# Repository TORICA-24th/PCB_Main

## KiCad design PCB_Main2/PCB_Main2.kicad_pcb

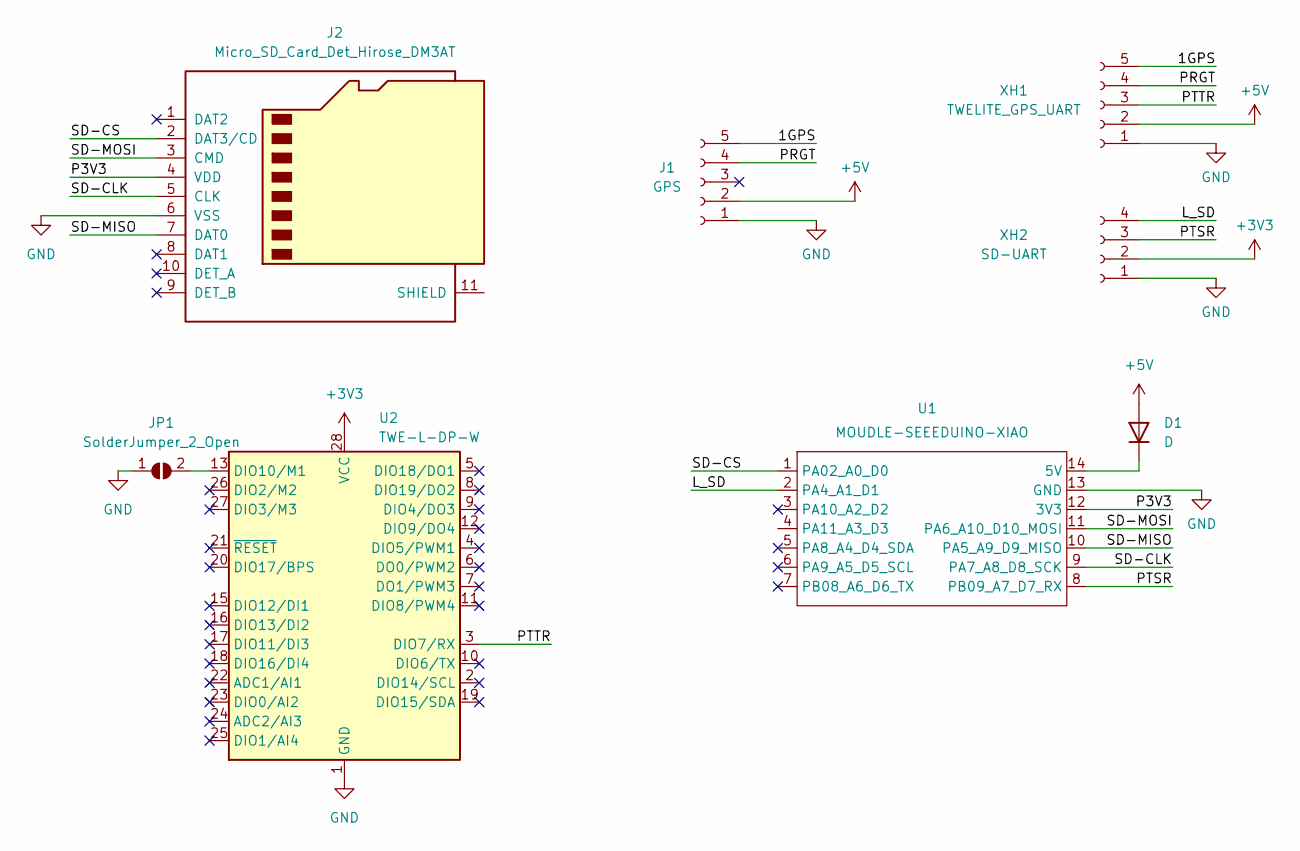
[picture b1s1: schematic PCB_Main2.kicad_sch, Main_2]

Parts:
D1: D; D_A-405_P10.16mm_Horizontal
J1: GPS; JST_XH_S5B-XH-A_1x05_P2.50mm_Horizontal
J2: Micro_SD_Card_Det_Hirose_DM3AT; microSD_AE-MICRO-SD-DIP
JP1: SolderJumper_2_Open; SolderJumper-2_P1.3mm_Open_RoundedPad1.0x1.5mm
U1: MOUDLE-SEEEDUINO-XIAO; MOUDLE14P-2.54-21X17.8MM
U2: TWE-L-DP-W; DIP-28_W15.24mm
XH1: TWELITE_GPS_UART; JST_XH_S5B-XH-A_1x05_P2.50mm_Horizontal
XH2: SD-UART; JST_XH_S4B-XH-A_1x04_P2.50mm_Horizontal

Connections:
+3V3: U2.28 (VCC), XH2.2
+5V: D1.2 (A), J1.2, XH1.2
/1GPS: J1.5, XH1.5
/L_SD: U1.2 (PA4_A1_D1), XH2.4
/P3V3: J2.4 (VDD), U1.12 (3V3)
/PRGT: J1.4, XH1.4
/PTSR: U1.8 (PB09_A7_D7_RX), XH2.3
/PTTR: U2.3 (DIO7/RX), XH1.3
/SD-CLK: J2.5 (CLK), U1.9 (PA7_A8_D8_SCK)
/SD-CS: J2.2 (DAT3/CD), U1.1 (PA02_A0_D0)
/SD-MISO: J2.7 (DAT0), U1.10 (PA5_A9_D9_MISO)
/SD-MOSI: J2.3 (CMD), U1.11 (PA6_A10_D10_MOSI)
GND: J1.1, J2.6 (VSS), JP1.1 (A), U1.13 (GND), U2.1 (GND), U2.14 (GND), XH1.1, XH2.1
unnamed: D1.1 (K), U1.14 (5V)
unnamed: JP1.2 (B), U2.13 (DIO10/M1)

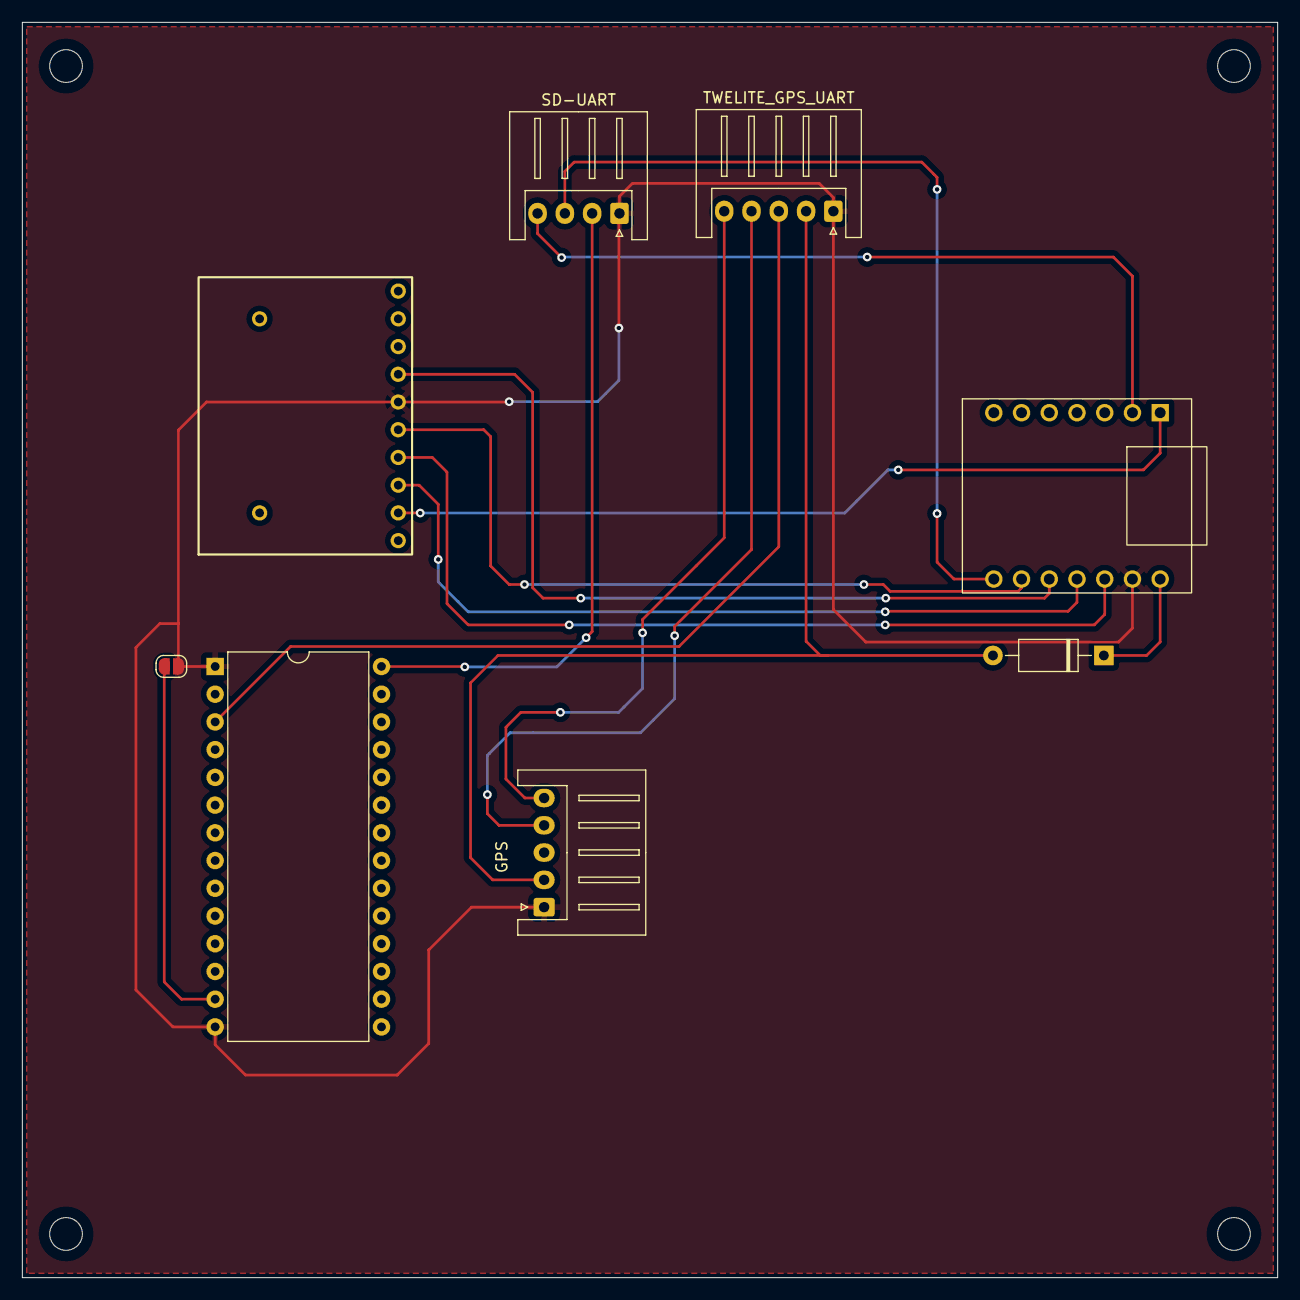
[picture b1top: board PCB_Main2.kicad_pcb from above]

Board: 2 copper layers, 115.0 x 115.0 mm, 8 parts (0 on the bottom side), 15 nets.

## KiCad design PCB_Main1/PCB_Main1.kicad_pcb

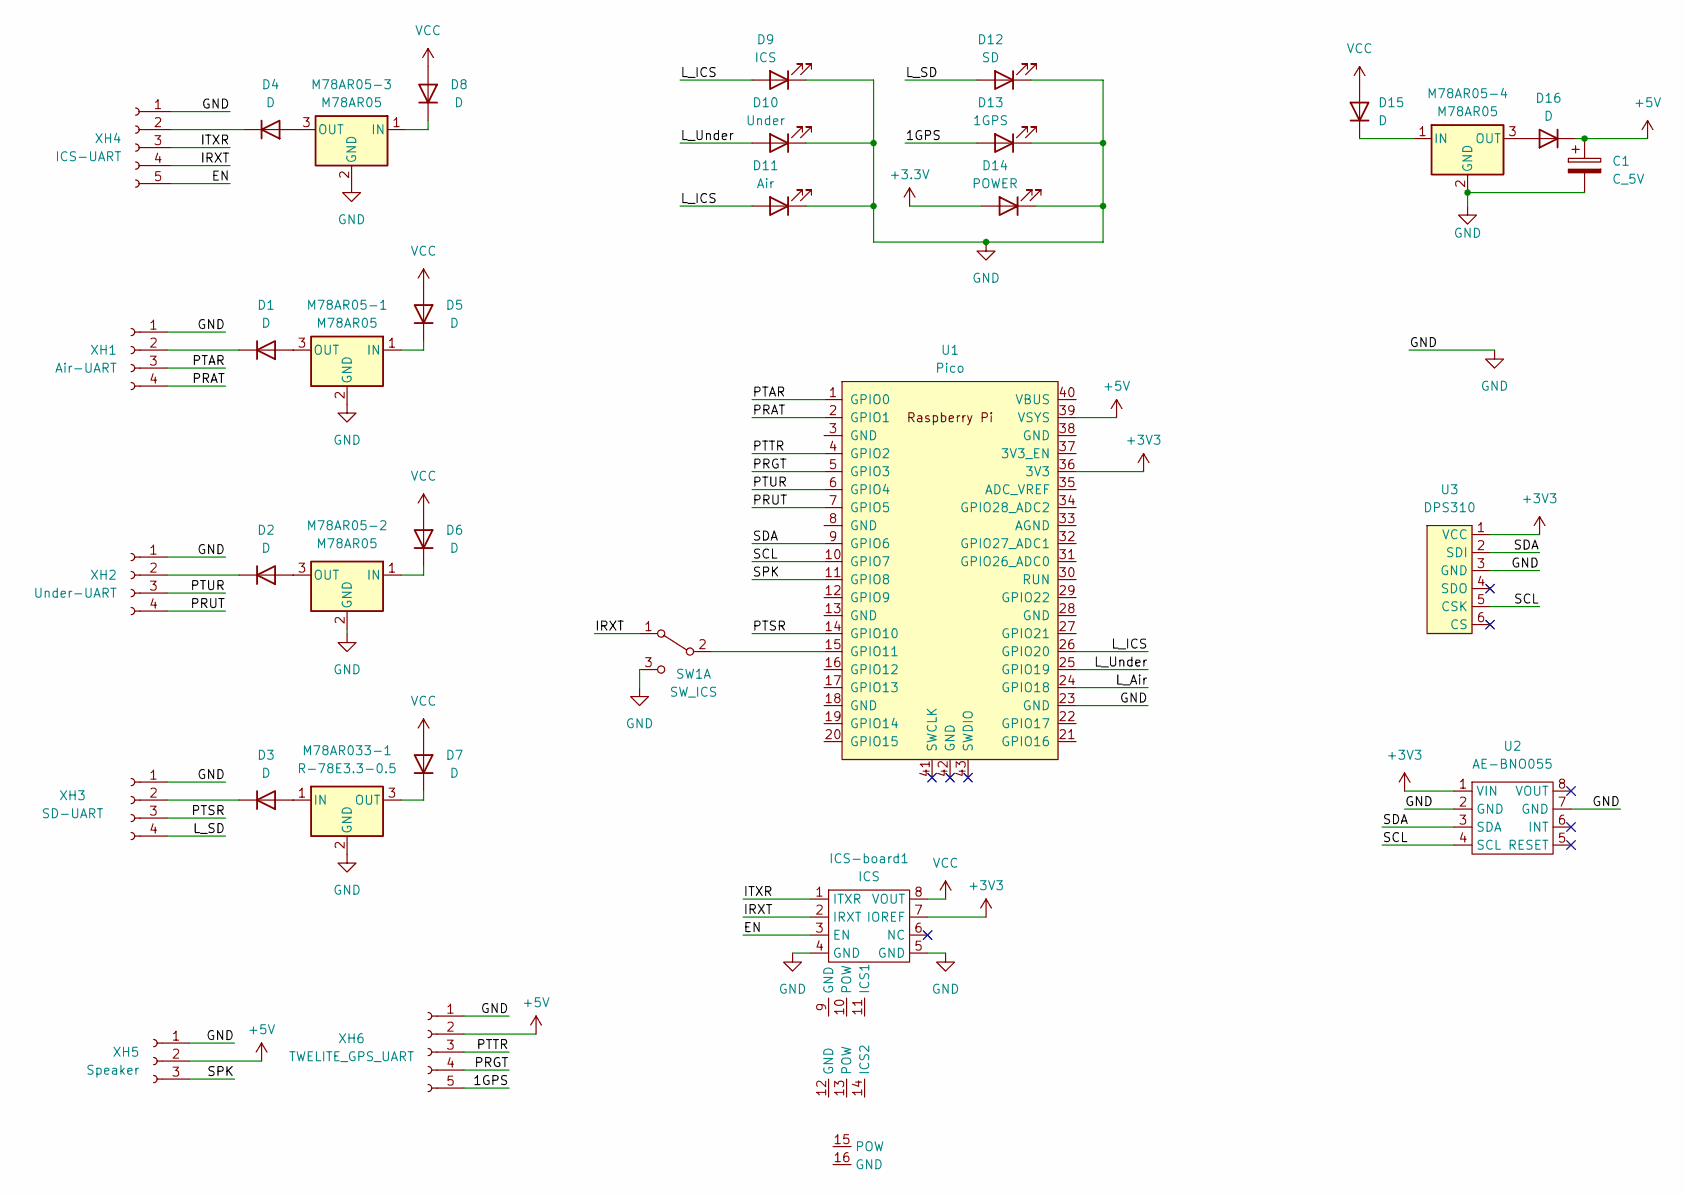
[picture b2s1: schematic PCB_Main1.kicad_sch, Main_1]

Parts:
C1: C_5V; CP_Radial_D5.0mm_P2.50mm
D1, D2, D3, D4, D5, D6, D7, D8, D15, D16: D; D_A-405_P10.16mm_Horizontal
D9: ICS; LED_D5.0mm
D10: Under; LED_D5.0mm
D11: Air; LED_D5.0mm
D12: SD; LED_D5.0mm
D13: 1GPS; LED_D5.0mm
D14: POWER; LED_D5.0mm
ICS-board1: ICS
M78AR05-1, M78AR05-2, M78AR05-3, M78AR05-4: M78AR05; Converter_DCDC_RECOM_R-78E-0.5_THT
M78AR033-1: R-78E3.3-0.5; Converter_DCDC_RECOM_R-78E-0.5_THT
SW1: SW_ICS; PinHeader_1x03_P2.54mm_Vertical
U1: Pico; RPi_Pico_SMD_TH
U2: AE-BNO055
U3: DPS310
XH1: Air-UART; JST_XH_S4B-XH-A_1x04_P2.50mm_Horizontal
XH2: Under-UART; JST_XH_S4B-XH-A_1x04_P2.50mm_Horizontal
XH3: SD-UART; JST_XH_S4B-XH-A_1x04_P2.50mm_Horizontal
XH4: ICS-UART; JST_XH_S5B-XH-A_1x05_P2.50mm_Horizontal
XH5: Speaker; JST_XH_S3B-XH-A_1x03_P2.50mm_Horizontal
XH6: TWELITE_GPS_UART; JST_XH_S5B-XH-A_1x05_P2.50mm_Horizontal

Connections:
+3.3V: D14.2 (A)
+3V3: ICS-board1.7 (IOREF), U1.36 (3V3), U2.1 (VIN), U3., U3.1 (VCC)
+5V: C1.1, D16.1 (K), U1.39 (VSYS), XH5.2, XH6.2
/1GPS: D13.2 (A), XH6.5
/EN: ICS-board1.3 (EN), XH4.5
/IRXT: ICS-board1.2 (IRXT), SW1.1 (A), XH4.4
/ITXR: ICS-board1.1 (ITXR), XH4.3
/L_Air: U1.24 (GPIO18)
/L_ICS: D9.2 (A), D11.2 (A), U1.26 (GPIO20)
/L_SD: D12.2 (A), XH3.4
/L_Under: D10.2 (A), U1.25 (GPIO19)
/PRAT: U1.2 (GPIO1), XH1.4
/PRGT: U1.5 (GPIO3), XH6.4
/PRUT: U1.7 (GPIO5), XH2.4
/PTAR: U1.1 (GPIO0), XH1.3
/PTSR: U1.14 (GPIO10), XH3.3
/PTTR: U1.4 (GPIO2), XH6.3
/PTUR: U1.6 (GPIO4), XH2.3
/SCL: U1.10 (GPIO7), U2.4 (SCL), U3.5 (CSK)
/SDA: U1.9 (GPIO6), U2.3 (SDA), U3.2 (SDI)
/SPK: U1.11 (GPIO8), XH5.3
GND: C1.2, D9.1 (K), D10.1 (K), D11.1 (K), D12.1 (K), D13.1 (K), D14.1 (K), ICS-board1.4 (GND), ICS-board1.5 (GND), M78AR05-1.2 (GND), M78AR05-2.2 (GND), M78AR05-3.2 (GND), M78AR05-4.2 (GND), M78AR033-1.2 (GND), SW1.3 (C), U1.23 (GND), U2.2 (GND), U2.7 (GND), U3.3 (GND), XH1.1, XH2.1, XH3.1, XH4.1, XH5.1, XH6.1
unnamed: D1.2 (A), M78AR05-1.3 (OUT)
unnamed: D1.1 (K), XH1.2
unnamed: D2.2 (A), M78AR05-2.3 (OUT)
unnamed: D2.1 (K), XH2.2
unnamed: D3.2 (A), M78AR033-1.1 (IN)
unnamed: D3.1 (K), XH3.2
unnamed: D4.2 (A), M78AR05-3.3 (OUT)
unnamed: D4.1 (K), XH4.2
unnamed: D5.1 (K), M78AR05-1.1 (IN)
unnamed: D6.1 (K), M78AR05-2.1 (IN)
unnamed: D7.1 (K), M78AR033-1.3 (OUT)
unnamed: D8.1 (K), M78AR05-3.1 (IN)
unnamed: D15.1 (K), M78AR05-4.1 (IN)
unnamed: D16.2 (A), M78AR05-4.3 (OUT)
unnamed: SW1.2 (B), U1.15 (GPIO11)
VCC: D5.2 (A), D6.2 (A), D7.2 (A), D8.2 (A), D15.2 (A), ICS-board1.8 (VOUT)

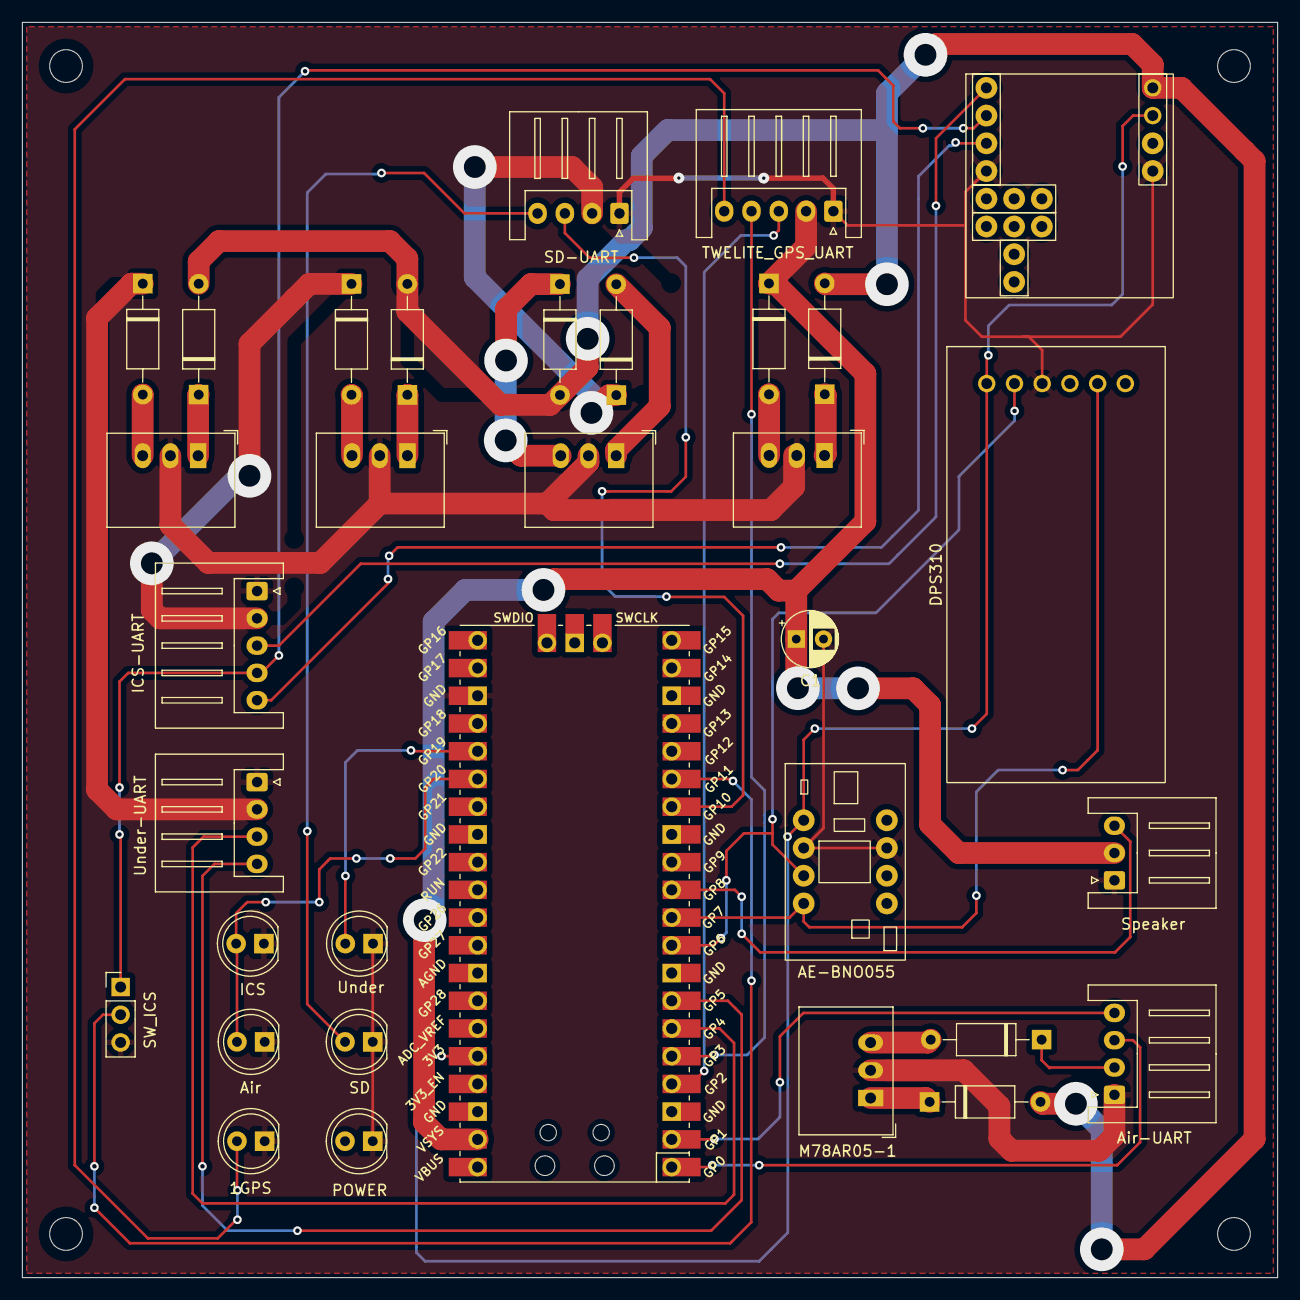
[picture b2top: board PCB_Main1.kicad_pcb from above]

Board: 2 copper layers, 115.0 x 115.0 mm, 33 parts (0 on the bottom side), 36 nets.

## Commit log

2023-11-03 update PCB_Main1.sch(1st create)
    1st create
2023-11-03 Do annotation
2023-11-03 update PCB_Main1 & PCB_Main2
2023-11-06 create backup
2023-11-07 add gyro sensor
2023-11-10 update main-1
2023-11-17 Update PCB_Main
2023-11-29 Update PCM_Main
2023-12-14 add backup
